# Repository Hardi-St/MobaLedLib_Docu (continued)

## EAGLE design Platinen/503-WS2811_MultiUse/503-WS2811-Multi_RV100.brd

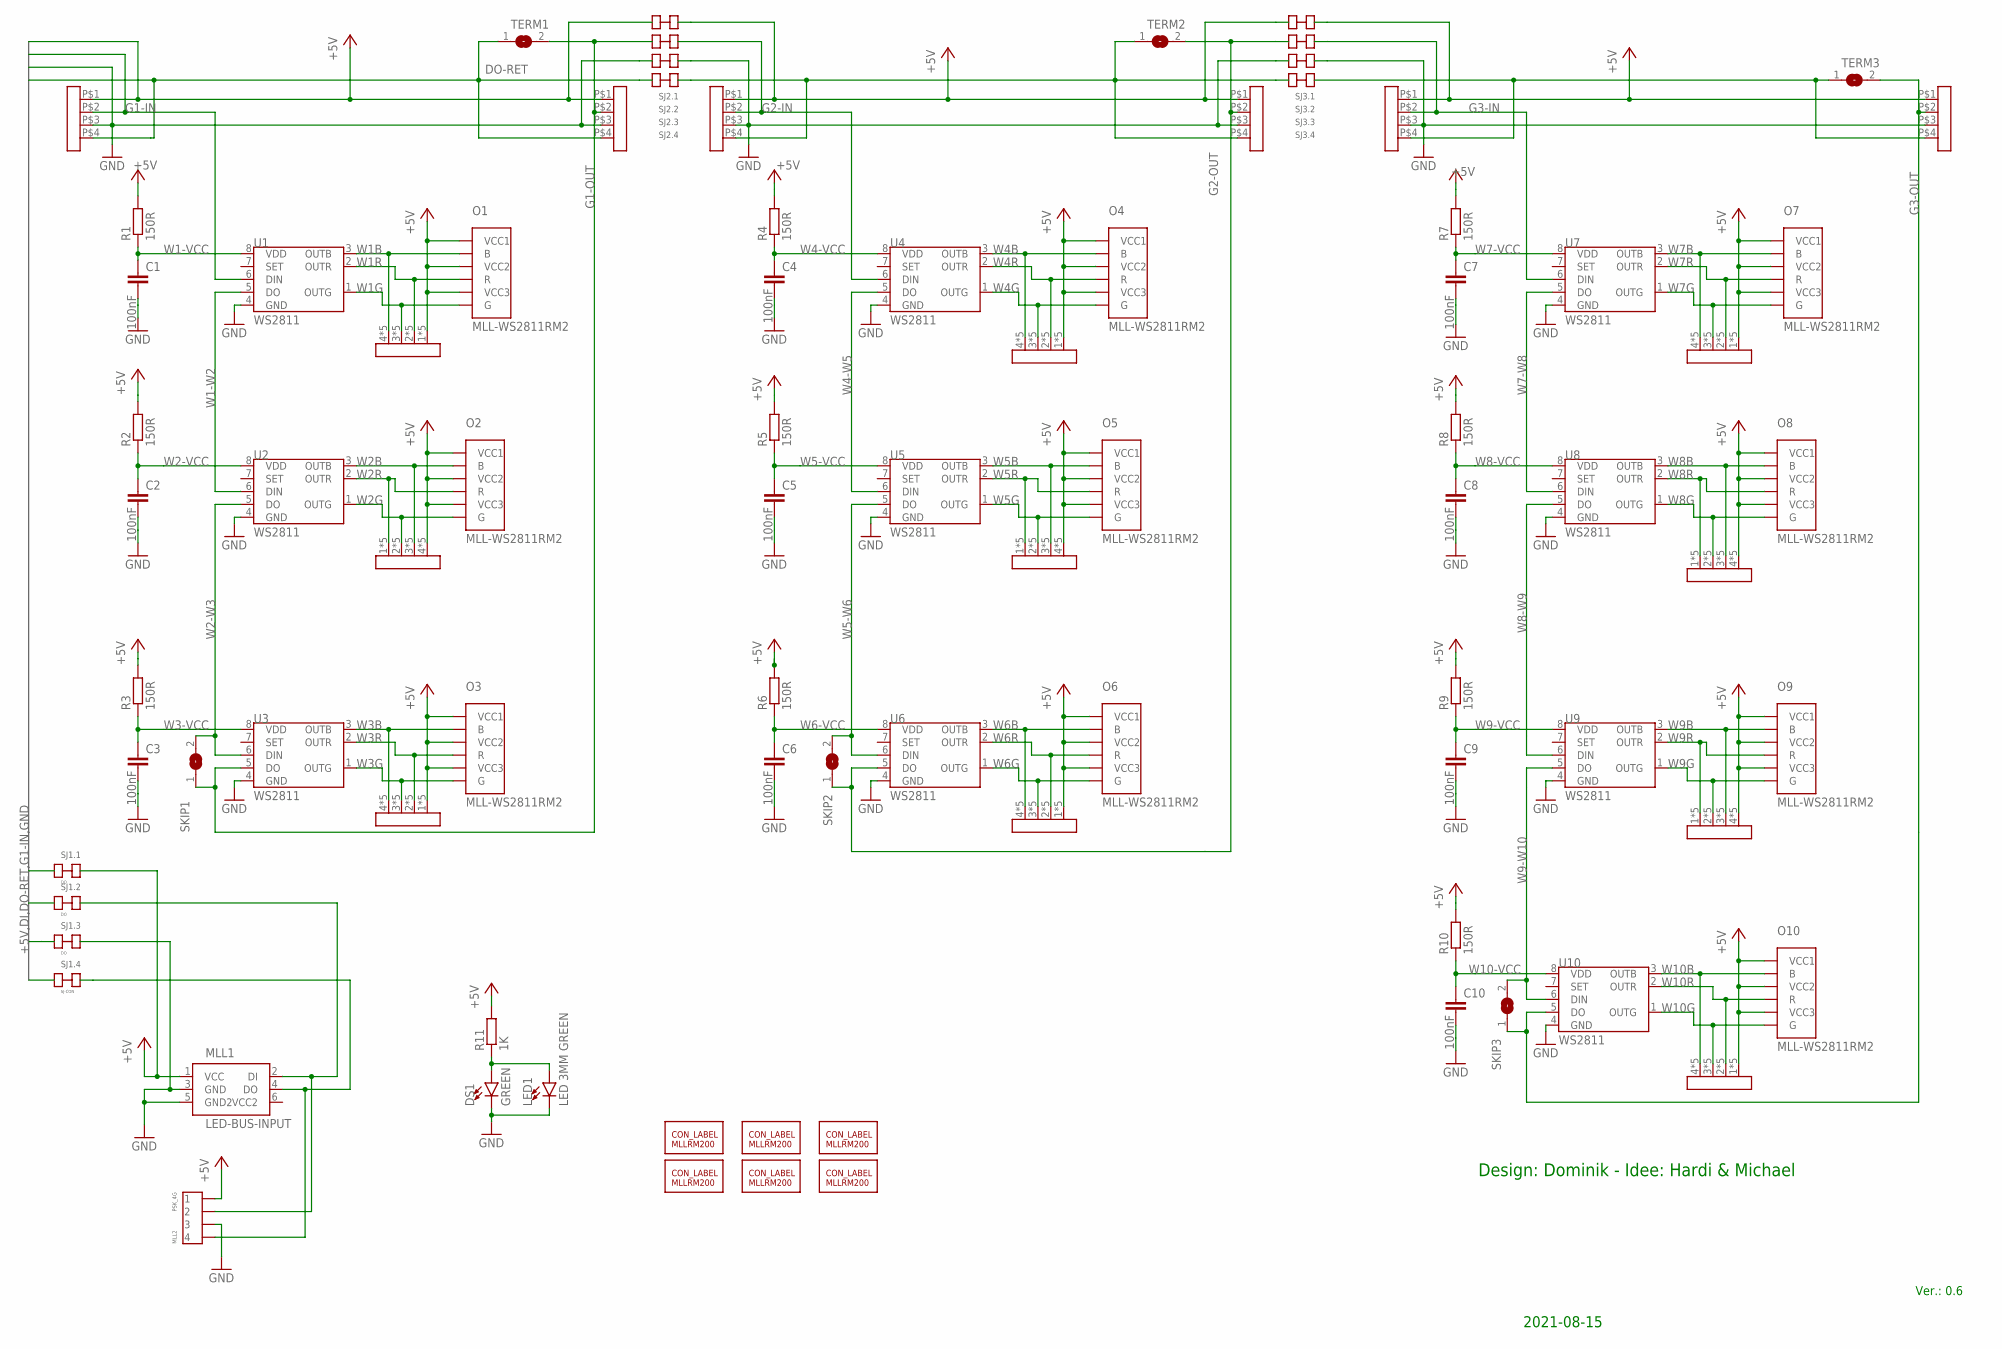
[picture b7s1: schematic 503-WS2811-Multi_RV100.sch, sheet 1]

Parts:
C1, C2, C3, C4, C5, C6, C7, C8, C9, C10: 100nF; C1206
DS1: GREEN; LED-1206
IN: 4XRM254
LED1: LED 3MM GREEN; LED_3MM
M1_IN, M1_OUT, M2_IN, M2_OUT: 4XRM254
MLL1: LED-BUS-INPUT; IDC6
MLL2: PSK_4G; PSSG4
O1, O2, O3, O4, O5, O6, O7, O8, O9, O10: MLL-WS2811RM2; MLL-WS2811-RM2
OUT: 4XRM254
R1, R2, R3, R4, R5, R6, R7, R8, R9, R10: 150R; R1206
R11: 1K; R1206
SJ1.1, SJ1.2, SJ1.3: DO; SJ-CON
SJ1.4, SJ2.1, SJ2.2, SJ2.3, SJ2.4, SJ3.1, SJ3.2, SJ3.3, SJ3.4: SJ-CON
SKIP1, SKIP2, SKIP3: SJ
TERM1, TERM2, TERM3: SJ
U1, U2, U3, U4, U5, U6, U7, U8, U9, U10: WS2811; SOP8
U$1, U$3, U$4: CON-LABEL_MLLRM200_2RGB_M; CON-LABEL_MLLRM200_RGB_M
U$2, U$6: CON-LABEL_MLLRM200_3
U$5: CON-LABEL_MLLRM200_2RGB; CON-LABEL_MLLRM200_RGB
U$7, U$8, U$9, U$14, U$15, U$16, U$17, U$18, U$19, U$20: 4XRM200LONG-NOH_DOUBLE; 4XRM200LONG_NOH_DOUBLE

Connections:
+5V: IN.P$1, M1_IN.P$1, M1_OUT.P$1, M2_IN.P$1, M2_OUT.P$1, MLL1.1 (VCC), MLL2.P$1 (1), O1.VCC1, O1.VCC2, O1.VCC3, O2.VCC1, O2.VCC2, O2.VCC3, O3.VCC1, O3.VCC2, O3.VCC3, O4.VCC1, O4.VCC2, O4.VCC3, O5.VCC1, O5.VCC2, O5.VCC3, O6.VCC1, O6.VCC2, O6.VCC3, O7.VCC1, O7.VCC2, O7.VCC3, O8.VCC1, O8.VCC2, O8.VCC3, O9.VCC1, O9.VCC2, O9.VCC3, O10.VCC1, O10.VCC2, O10.VCC3, OUT.P$1, R1.2, R2.2, R3.2, R4.2, R5.2, R6.2, R7.2, R8.2, R9.2, R10.2, R11.2, SJ1.1.P$1, SJ1.1.P$2, SJ2.1.P$1, SJ2.1.P$2, SJ3.1.P$1, SJ3.1.P$2, U$7.1, U$7.1B, U$7.11, U$7.12, U$7.13, U$8.4, U$8.4B, U$8.41, U$8.42, U$8.43, U$9.1, U$9.1B, U$9.11, U$9.12, U$9.13, U$14.1, U$14.1B, U$14.11, U$14.12, U$14.13, U$15.4, U$15.4B, U$15.41, U$15.42, U$15.43, U$16.1, U$16.1B, U$16.11, U$16.12, U$16.13, U$17.1, U$17.1B, U$17.11, U$17.12, U$17.13, U$18.4, U$18.4B, U$18.41, U$18.42, U$18.43, U$19.4, U$19.4B, U$19.41, U$19.42, U$19.43, U$20.1, U$20.1B, U$20.11, U$20.12, U$20.13
DI: MLL1.2 (DI), MLL2.P$2 (2), SJ1.2.P$2
DO: MLL1.4 (DO), MLL2.P$4 (4), SJ1.4.P$2
DO-RET: M1_IN.P$4, M1_OUT.P$4, SJ1.4.P$1, SJ2.4.P$1, TERM1.1
G1-IN: M1_IN.P$2, SJ1.2.P$1, U1.6 (DIN)
G1-OUT: M1_OUT.P$2, SJ2.2.P$1, SKIP1.1, TERM1.2, U3.5 (DO)
G2-IN: M2_IN.P$2, SJ2.2.P$2, U4.6 (DIN)
G2-OUT: M2_OUT.P$2, SJ3.2.P$1, SKIP2.1, TERM2.2, U6.5 (DO)
G2-RET: M2_IN.P$4, M2_OUT.P$4, SJ2.4.P$2, SJ3.4.P$1, TERM2.1
G3-IN: IN.P$2, SJ3.2.P$2, U7.6 (DIN)
G3-OUT: OUT.P$2, SKIP3.1, TERM3.2, U10.5 (DO)
G3-RET: IN.P$4, OUT.P$4, SJ3.4.P$2, TERM3.1
GND: C1.2, C2.2, C3.2, C4.2, C5.2, C6.2, C7.2, C8.2, C9.2, C10.2, DS1.C, IN.P$3, LED1.K (C), M1_IN.P$3, M1_OUT.P$3, M2_IN.P$3, M2_OUT.P$3, MLL1.3 (GND), MLL1.5 (GND2), MLL2.P$3 (3), OUT.P$3, SJ1.3.P$1, SJ1.3.P$2, SJ2.3.P$1, SJ2.3.P$2, SJ3.3.P$1, SJ3.3.P$2, U1.4 (GND), U2.4 (GND), U3.4 (GND), U4.4 (GND), U5.4 (GND), U6.4 (GND), U7.4 (GND), U8.4 (GND), U9.4 (GND), U10.4 (GND)
LED1: DS1.A, LED1.A, R11.1
VCC2: MLL1.6 (VCC2)
W1-VCC: C1.1, R1.1, U1.8 (VDD)
W1-W2: U1.5 (DO), U2.6 (DIN)
W1B: O1.B, U1.3 (OUTB), U$9.4, U$9.4B, U$9.41, U$9.42, U$9.43
W1G: O1.G, U1.1 (OUTG), U$9.3, U$9.3B, U$9.31, U$9.32, U$9.33
W1R: O1.R, U1.2 (OUTR), U$9.2, U$9.2B, U$9.21, U$9.22, U$9.23
W2-VCC: C2.1, R2.1, U2.8 (VDD)
W2-W3: SKIP1.2, U2.5 (DO), U3.6 (DIN)
W2B: O2.B, U2.3 (OUTB), U$8.3, U$8.3B, U$8.31, U$8.32, U$8.33
W2G: O2.G, U2.1 (OUTG), U$8.2, U$8.2B, U$8.21, U$8.22, U$8.23
W2R: O2.R, U2.2 (OUTR), U$8.1, U$8.1B, U$8.11, U$8.12, U$8.13
W3-VCC: C3.1, R3.1, U3.8 (VDD)
W3B: O3.B, U3.3 (OUTB), U$7.4, U$7.4B, U$7.41, U$7.42, U$7.43
W3G: O3.G, U3.1 (OUTG), U$7.3, U$7.3B, U$7.31, U$7.32, U$7.33
W3R: O3.R, U3.2 (OUTR), U$7.2, U$7.2B, U$7.21, U$7.22, U$7.23
W4-VCC: C4.1, R4.1, U4.8 (VDD)
W4-W5: U4.5 (DO), U5.6 (DIN)
W4B: O4.B, U4.3 (OUTB), U$14.4, U$14.4B, U$14.41, U$14.42, U$14.43
W4G: O4.G, U4.1 (OUTG), U$14.3, U$14.3B, U$14.31, U$14.32, U$14.33
W4R: O4.R, U4.2 (OUTR), U$14.2, U$14.2B, U$14.21, U$14.22, U$14.23
W5-VCC: C5.1, R5.1, U5.8 (VDD)
W5-W6: SKIP2.2, U5.5 (DO), U6.6 (DIN)
W5B: O5.B, U5.3 (OUTB), U$15.3, U$15.3B, U$15.31, U$15.32, U$15.33
W5G: O5.G, U5.1 (OUTG), U$15.2, U$15.2B, U$15.21, U$15.22, U$15.23
W5R: O5.R, U5.2 (OUTR), U$15.1, U$15.1B, U$15.11, U$15.12, U$15.13
W6-VCC: C6.1, R6.1, U6.8 (VDD)
W6B: O6.B, U6.3 (OUTB), U$16.4, U$16.4B, U$16.41, U$16.42, U$16.43
W6G: O6.G, U6.1 (OUTG), U$16.3, U$16.3B, U$16.31, U$16.32, U$16.33
W6R: O6.R, U6.2 (OUTR), U$16.2, U$16.2B, U$16.21, U$16.22, U$16.23
W7-VCC: C7.1, R7.1, U7.8 (VDD)
W7-W8: U7.5 (DO), U8.6 (DIN)
W7B: O7.B, U7.3 (OUTB), U$17.4, U$17.4B, U$17.41, U$17.42, U$17.43
W7G: O7.G, U7.1 (OUTG), U$17.3, U$17.3B, U$17.31, U$17.32, U$17.33
W7R: O7.R, U7.2 (OUTR), U$17.2, U$17.2B, U$17.21, U$17.22, U$17.23
W8-VCC: C8.1, R8.1, U8.8 (VDD)
W8-W9: U8.5 (DO), U9.6 (DIN)
W8B: O8.B, U8.3 (OUTB), U$18.3, U$18.3B, U$18.31, U$18.32, U$18.33
W8G: O8.G, U8.1 (OUTG), U$18.2, U$18.2B, U$18.21, U$18.22, U$18.23
W8R: O8.R, U8.2 (OUTR), U$18.1, U$18.1B, U$18.11, U$18.12, U$18.13
W9-VCC: C9.1, R9.1, U9.8 (VDD)
W9-W10: SKIP3.2, U9.5 (DO), U10.6 (DIN)
W9B: O9.B, U9.3 (OUTB), U$19.3, U$19.3B, U$19.31, U$19.32, U$19.33
W9G: O9.G, U9.1 (OUTG), U$19.2, U$19.2B, U$19.21, U$19.22, U$19.23
W9R: O9.R, U9.2 (OUTR), U$19.1, U$19.1B, U$19.11, U$19.12, U$19.13
W10-VCC: C10.1, R10.1, U10.8 (VDD)
W10B: O10.B, U10.3 (OUTB), U$20.4, U$20.4B, U$20.41, U$20.42, U$20.43
W10G: O10.G, U10.1 (OUTG), U$20.3, U$20.3B, U$20.31, U$20.32, U$20.33
W10R: O10.R, U10.2 (OUTR), U$20.2, U$20.2B, U$20.21, U$20.22, U$20.23

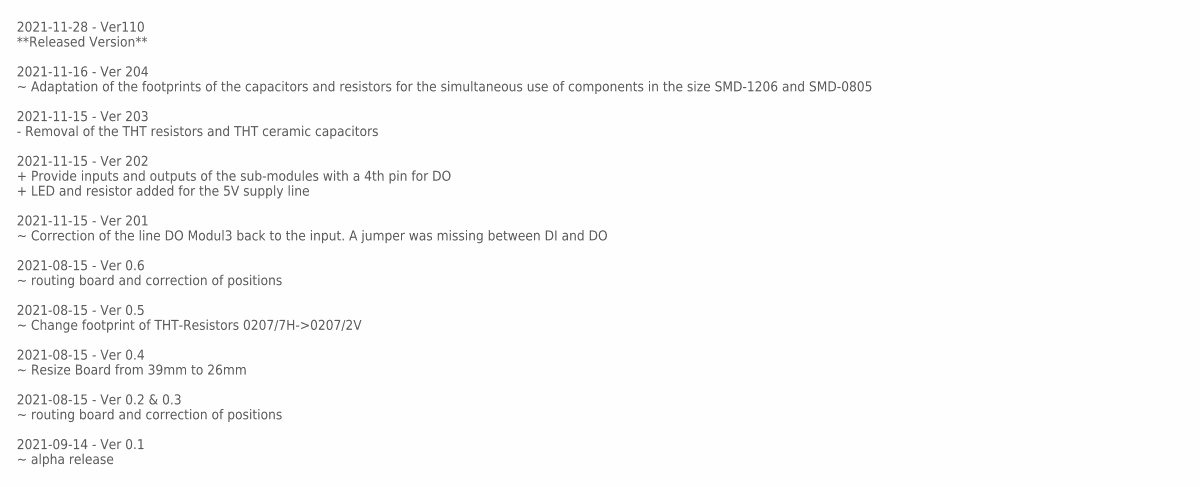
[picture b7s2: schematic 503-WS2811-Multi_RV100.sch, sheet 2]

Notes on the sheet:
2021-11-28 - Ver110 **Released Version** 2021-11-16 - Ver 204 ~ Adaptation of the footprints of the capacitors and resistors for the simultaneous use of components in the size SMD-1206 and SMD-0805 2021-11-15 - Ver 203 - Removal of the THT resistors and THT ceramic capacitors 2021-11-15 - Ver 202 +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

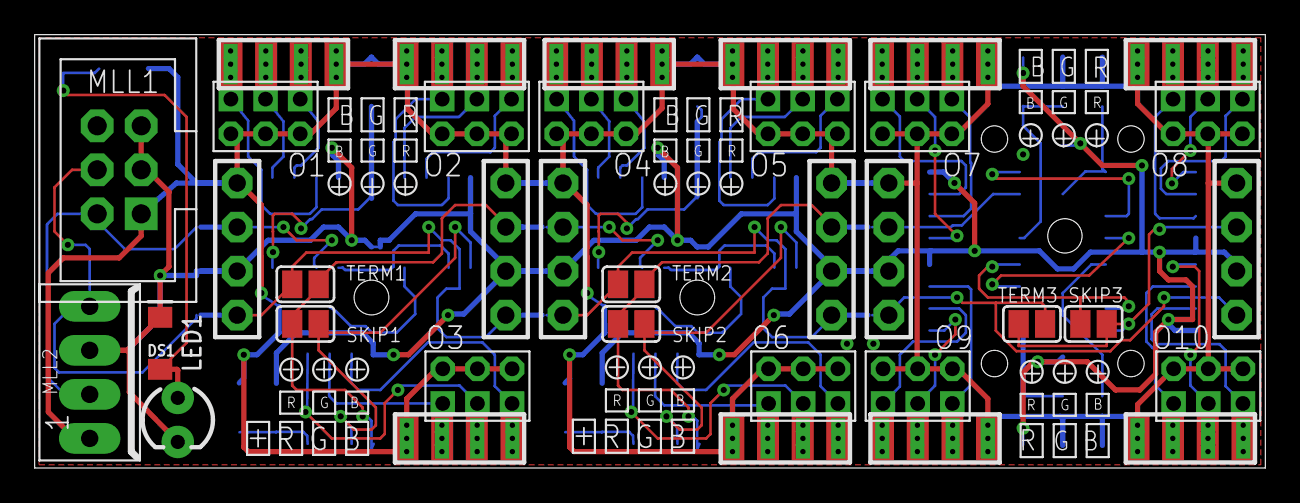
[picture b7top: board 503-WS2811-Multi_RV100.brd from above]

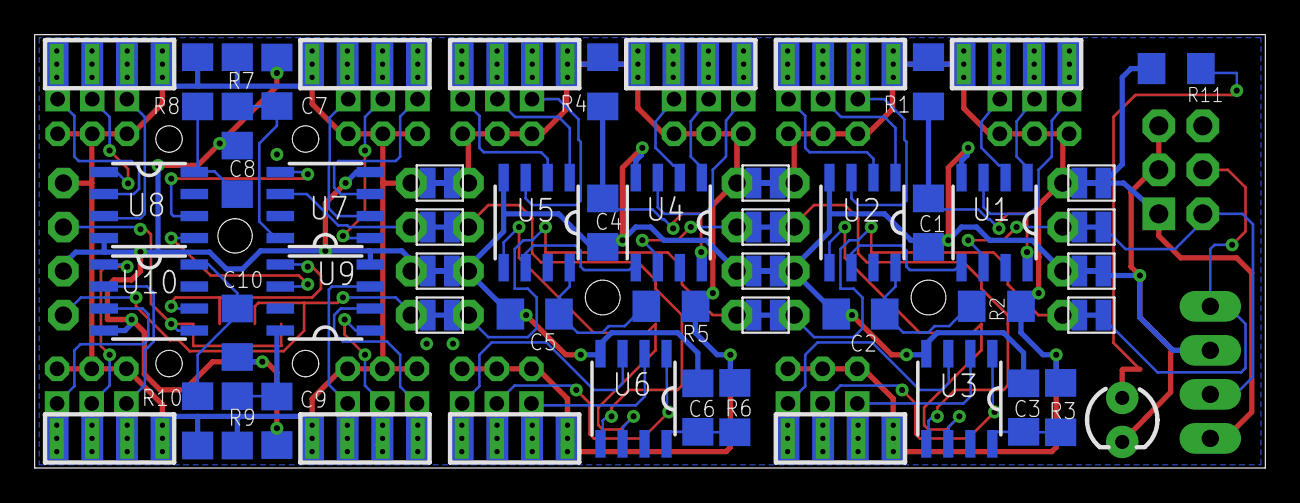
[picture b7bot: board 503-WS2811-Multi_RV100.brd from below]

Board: 2 copper layers, 71.0 x 25.0 mm, 85 parts (44 on the bottom side), 61 nets.

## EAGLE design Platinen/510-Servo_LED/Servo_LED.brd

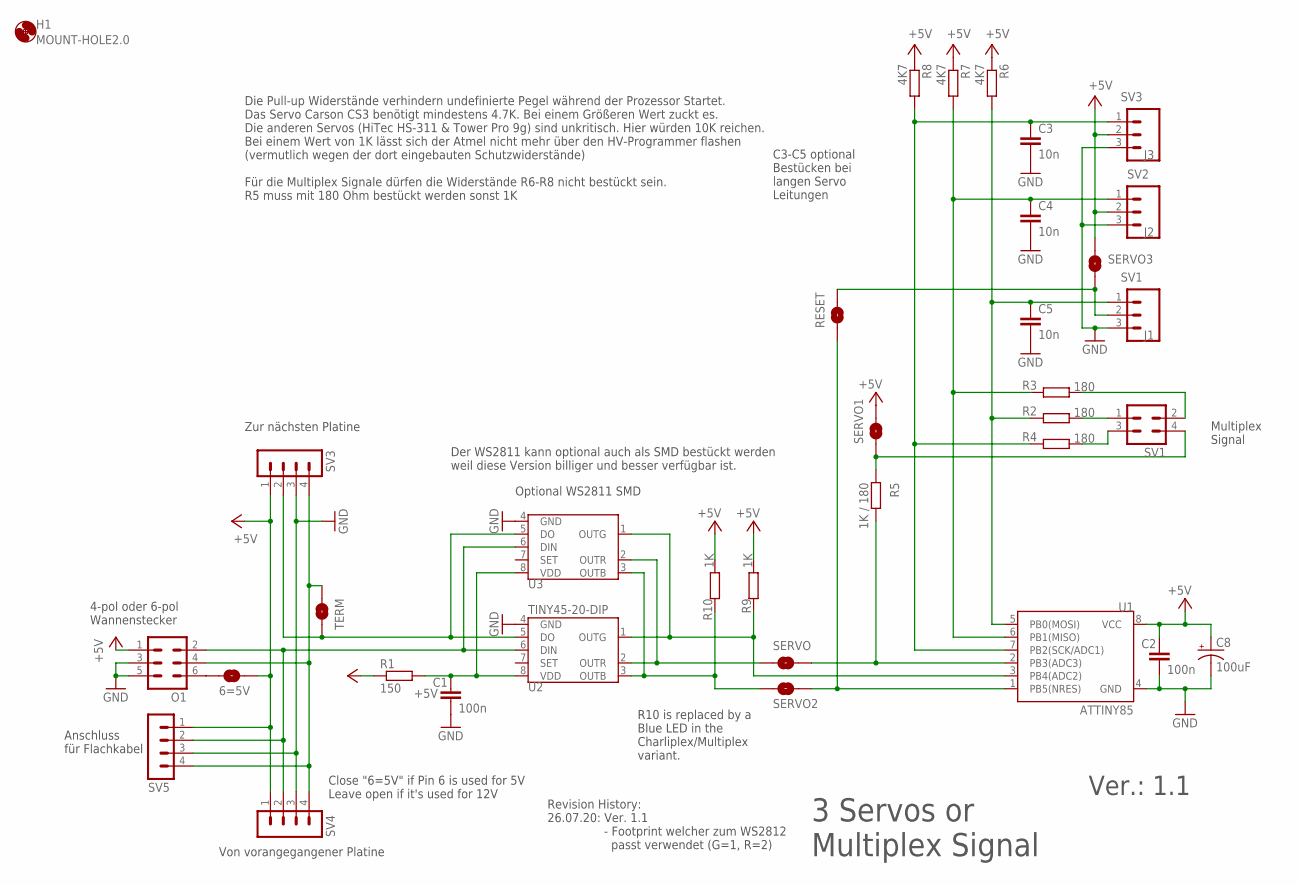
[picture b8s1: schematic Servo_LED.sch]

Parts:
6=5V: SOLDERJUMPERNO; SJ_2S-NO
C1, C2: 100n; C025-024X044
C3, C4, C5: 10n; C0805
C8: 100uF; SPARKFUN-CAPACITORS_CPOL-RADIAL-100UF-25V
H1: MOUNT-HOLE2.0; 2,0
J1: SV1; 1X03
J2: SV2; 1X03
J3: SV3; 1X03
O1: ML6
R1: 150; RCL_0207/2V
R2, R3, R4: 180; RCL_0207/2V
R5: 1K / 180; RCL_0207/2V
R6, R7, R8: 4K7; RCL_0207/2V
R9, R10: 1K; RCL_0207/2V
RESET: SOLDERJUMPERNO; SJ_2S-NO
SERVO, SERVO1, SERVO2, SERVO3: SOLDERJUMPERNO; SJ_2S-NO
SV1: MA02-2MUX-SIGNAL; MUX-SIGNAL
SV3, SV4, SV5: MA04-1
TERM: SOLDERJUMPERNO; SJ_2S-NO
U1: ATTINY85; DIP08
U2: TINY45-20-DIP; S3PO_MODUL_WS2811_SOUND_MP3-TF-16P_WS2811_AND_ATTINY_WS2811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
U3: WS2811 SOT-8; SOP8

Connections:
+5V: 6=5V.2, C2.1, C8.1 (+), J2.2, J3.2, O1.1, R1.1, R6.1, R7.1, R8.1, R9.1, R10.1, SERVO1.2, SERVO3.2, SV3.1, SV4.1, SV5.1, U1.8 (VCC)
GND: C1.2, C2.2, C3.2, C4.2, C5.2, C8.2 (-), J1.3, J2.3, J3.3, O1.3, O1.5, SV3.3, SV4.3, SV5.3, U1.4 (GND), U2.4 (GND), U3.4 (GND)
unnamed: O1.2, SV4.2, SV5.2, U2.6 (DIN), U3.6 (DIN)
unnamed: SV3.2, TERM.2, U2.5 (DO), U3.5 (DO)
unnamed: O1.4, SV3.4, SV4.4, SV5.4, TERM.1
unnamed: C1.1, R1.2, U2.8 (VDD), U3.8 (VDD)
unnamed: R2.1, SV1.1
unnamed: 6=5V.1, O1.6
unnamed: R9.2, U1.3 (PB4(ADC2)), U2.1 (OUTG), U3.1 (OUTG)
unnamed: R5.2, SERVO.2, U1.2 (PB3(ADC3))
unnamed: C4.1, J2.1, R3.2, R7.2, U1.6 (PB1(MISO))
unnamed: R4.1, SV1.3
unnamed: R3.1, SV1.2
unnamed: R5.1, SERVO1.1, SV1.4
unnamed: SERVO.1, U2.2 (OUTR), U3.2 (OUTR)
unnamed: C3.1, J3.1, R4.2, R8.2, U1.7 (PB2(SCK/ADC1))
unnamed: RESET.1, SERVO2.2, U1.1 (PB5(NRES))
unnamed: C5.1, J1.1, R2.2, R6.2, U1.5 (PB0(MOSI))
unnamed: J1.2, RESET.2, SERVO3.1
unnamed: R10.2, SERVO2.1, U2.3 (OUTB), U3.3 (OUTB)

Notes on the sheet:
Anschluss für Flachkabel
4-pol oder 6-pol Wannenstecker
Multiplex Signal
3 Servos or Multiplex Signal
Close "6=5V" if Pin 6 is used for 5V Leave open if it's used for 12V
C3-C5 optional Bestücken bei langen Servo Leitungen
Die Pull-up Widerstände verhindern undefinierte Pegel während der Prozessor Startet. Das Servo Carson CS3 benötigt mindestens 4.7K. Bei einem Größeren Wert zuckt es. Die anderen Servos (HiTec HS-311 & Tower Pro 9g) sind unkritisch. Hier würden 10K reichen. Bei einem Wert von 1K lässt sich der Atmel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
Optional WS2811 SMD
Zur nächsten Platine
Von vorangegangener Platine
Der WS2811 kann optional auch als SMD bestückt werden weil diese Version billiger und besser verfügbar ist.
R10 is replaced by a Blue LED in the Charliplex/Multiplex variant.
Ver.: 1.1
Revision History: 26.07.20: Ver. 1.1 - Footprint welcher zum WS2812 passt verwendet (G=1, R=2)

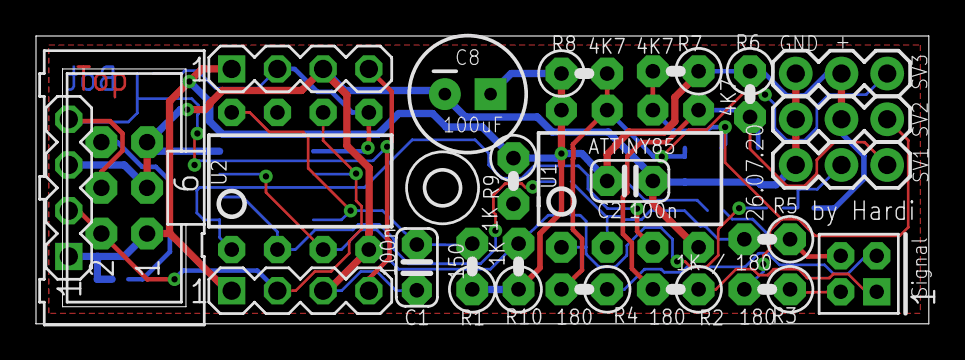
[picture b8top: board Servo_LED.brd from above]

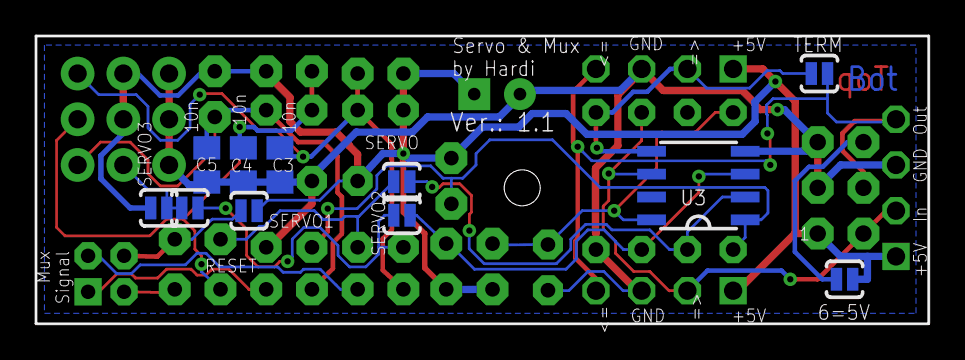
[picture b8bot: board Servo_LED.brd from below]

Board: 2 copper layers, 49.6 x 16.0 mm, 35 parts (11 on the bottom side), 20 nets.
